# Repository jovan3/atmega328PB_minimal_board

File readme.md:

# Atmega328PB-AU Minimal board

A Kicad project for an Atmega328PB-AU minimal board. I got a few of these microcontrollers and I read that they have some interesting features that Atmega328Ps don't have, such as additional USART, SPI, Timers, etc.

## Programming

There's a 10-pin AVR ICSP header. I used USBASP with Arduino to burn an Arduino bootloader and flash a sketch. I used [this](https://github.com/watterott/ATmega328PB-Testing) github project to get the Atmega328PB board definition files working and used the "Atmega328PB Internal Clock" with the 8MHz option to flash the bootloader. The microcontroller board has a crystal oscillator. If it's populated with a 16MHz crystal, for example, the microcontroller can be programmed to use that. You can use any of the six exposed microcontroller pins (23-26, 30, 31) to connect an LED for example, to test with a Blink Hello World program.

## Preview

Here's a 3D rendering of the board viewed from above, so you can see how it looks like without importing the project in Kicad:

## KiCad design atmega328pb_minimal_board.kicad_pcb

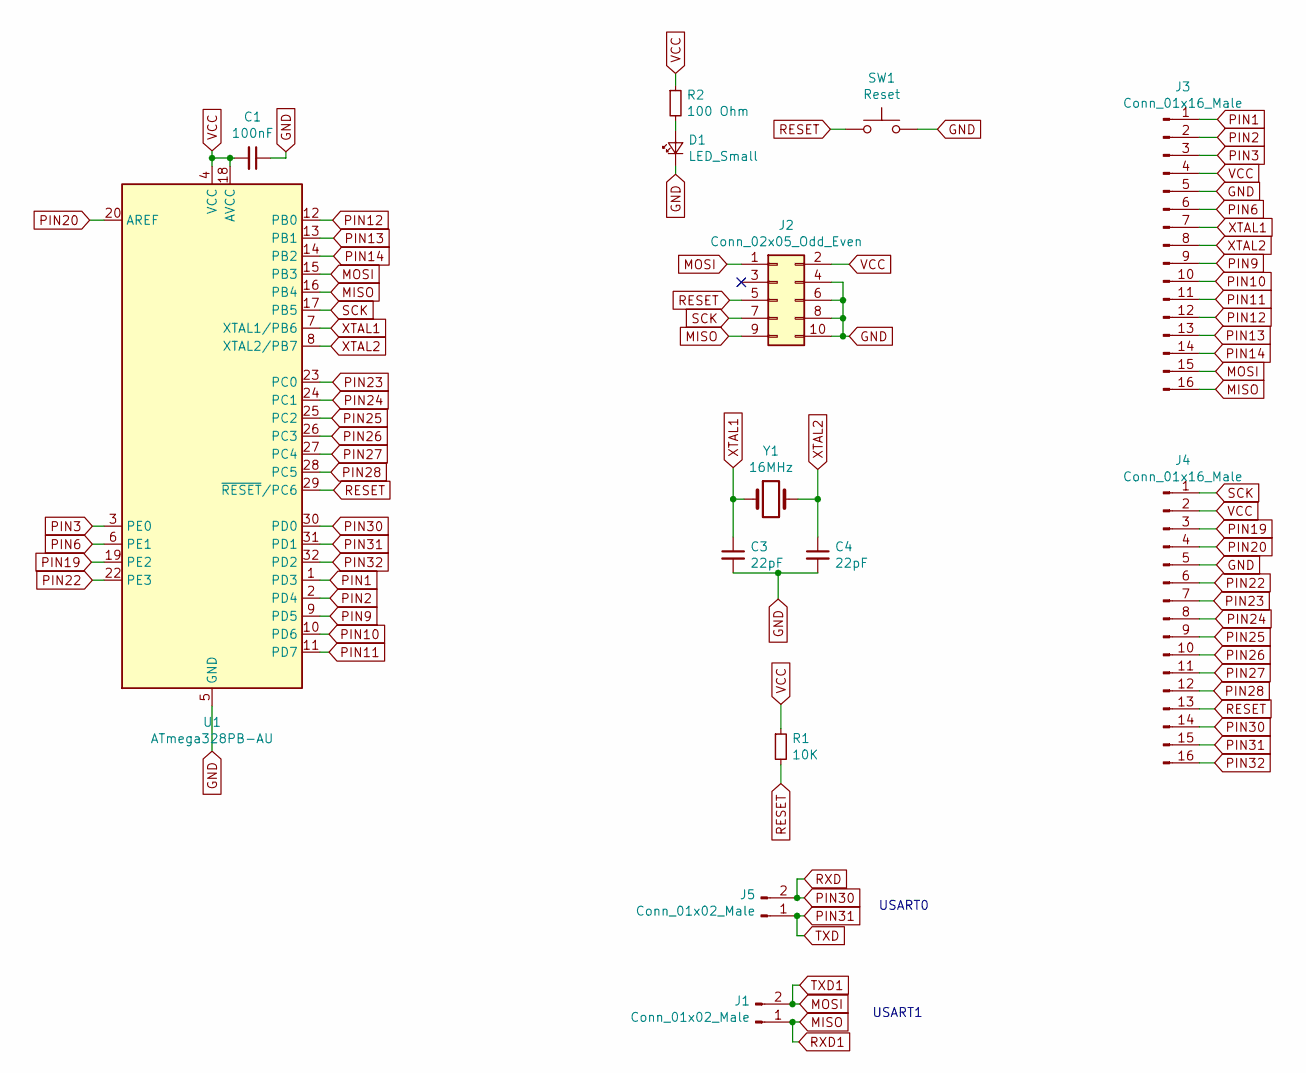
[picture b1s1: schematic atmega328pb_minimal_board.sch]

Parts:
C1: 100nF; C_0805_2012Metric_Pad1.15x1.40mm_HandSolder
C3, C4: 22pF; C_0805_2012Metric_Pad1.15x1.40mm_HandSolder
D1: LED_Small; LED_0805_2012Metric_Pad1.15x1.40mm_HandSolder
J1, J5: Conn_01x02_Male; PinHeader_1x02_P2.54mm_Vertical
J2: Conn_02x05_Odd_Even; PinHeader_2x05_P2.54mm_Vertical
J3, J4: Conn_01x16_Male; PinSocket_1x16_P2.54mm_Vertical
R1: 10K; R_0805_2012Metric_Pad1.15x1.40mm_HandSolder
R2: 100 Ohm; R_0805_2012Metric_Pad1.15x1.40mm_HandSolder
SW1: Reset; SW_PUSH_6mm_H5mm
U1: ATmega328PB-AU; TQFP-32_7x7mm_P0.8mm
Y1: 16MHz; Crystal_HC49-4H_Vertical

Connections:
GND: C1.1, C3.2, C4.2, D1.1 (K), J2.4, J2.6, J2.8, J2.10, J3.5, J4.5, SW1.2, U1.5 (GND), U1.21 (GND); also elsewhere on the board
MISO: J1.1, J2.9, J3.16, U1.16 (PB4)
MOSI: J1.2, J2.1, J3.15, U1.15 (PB3)
unnamed: D1.2 (A), R2.2
PIN1: J3.1, U1.1 (PD3)
PIN2: J3.2, U1.2 (PD4)
PIN3: J3.3, U1.3 (PE0)
PIN6: J3.6, U1.6 (PE1)
PIN9: J3.9, U1.9 (PD5)
PIN10: J3.10, U1.10 (PD6)
PIN11: J3.11, U1.11 (PD7)
PIN12: J3.12, U1.12 (PB0)
PIN13: J3.13, U1.13 (PB1)
PIN14: J3.14, U1.14 (PB2)
PIN19: J4.3, U1.19 (PE2)
PIN20: J4.4, U1.20 (AREF)
PIN22: J4.6, U1.22 (PE3)
PIN23: J4.7, U1.23 (PC0)
PIN24: J4.8, U1.24 (PC1)
PIN25: J4.9, U1.25 (PC2)
PIN26: J4.10, U1.26 (PC3)
PIN27: J4.11, U1.27 (PC4)
PIN28: J4.12, U1.28 (PC5)
PIN30: J4.14, J5.2, U1.30 (PD0)
PIN31: J4.15, J5.1, U1.31 (PD1)
PIN32: J4.16, U1.32 (PD2)
RESET: J2.5, J4.13, R1.2, SW1.1, U1.29 (~RESET~/PC6); also elsewhere on the board
SCK: J2.7, J4.1, U1.17 (PB5)
VCC: C1.2, J2.2, J3.4, J4.2, R1.1, R2.1, U1.4 (VCC), U1.18 (AVCC)
XTAL1: C3.1, J3.7, U1.7 (XTAL1/PB6), Y1.1
XTAL2: C4.1, J3.8, U1.8 (XTAL2/PB7), Y1.2

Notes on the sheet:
USART0
USART1

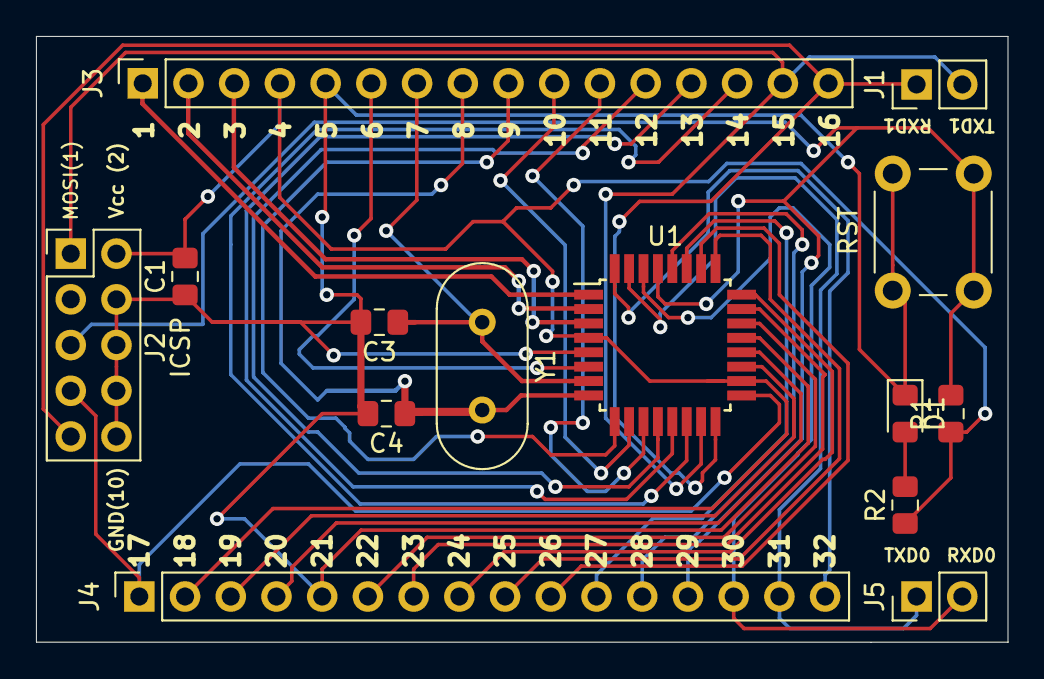
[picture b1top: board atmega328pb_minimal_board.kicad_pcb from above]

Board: 2 copper layers, 54.0 x 33.7 mm, 14 parts (0 on the bottom side), 31 nets.

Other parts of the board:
RST: Reset; SW_PUSH_6mm_H5mm

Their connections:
GND: RST.2; also elsewhere on the board
RESET: RST.1; also elsewhere on the board

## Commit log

2019-08-15 add docs
2019-08-23 change board layout
2019-08-23 add reset button, two usart headers and an LED
2019-08-28 change 2 1x16 male pin headers to female connectors
2019-08-28 add some pin labels
2019-09-11 add board 3d rendering image for github
2019-09-11 remove old gerber and pdf files
2020-06-23 update front silkscreen around the ICSP. Update docs.
